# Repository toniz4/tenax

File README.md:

# Tenax

Tenax is a direct pin/diodeless split keyboard, based on the Blackpill dev board. with pinkie splay.

## Pictures

## Features

- No diodes
- Simple
  - No rgb
  - No oled
  - No buzzer (why someone would use this)
  - No having fun
- Cheap to build
- Moderate stagger
- Pinkie splay
- More memory, storage and clock than pro micro based boards
- Simple and comparatively fast to build

## Bill of Materials

| Component | Quantity | Comment |
|----------|-------------|------|
| Blackpill | 2 | [Weact Blackpills](https://pt.aliexpress.com/item/1005001456186625.html?spm=a2g0o.cart.0.0.4bff7f06OmOHkX&mp=1&gatewayAdapt=glo2bra) |
| (Optional) Round socket headers | 4 pieces with 20 slots | [Sockets](https://pt.aliexpress.com/item/32849903666.html?spm=a2g0o.productlist.0.0.5d201206BfLSLq&algo_pvid=ee920bf7-0efe-47ff-ae7a-32ff20382c14&algo_exp_id=ee920bf7-0efe-47ff-ae7a-32ff20382c14-2&pdp_ext_f=%7B%22sku_id%22%3A%2265196146337%22%7D&pdp_npi=2%40dis%21BRL%216.85%216.17%21%21%2122.31%21%21%402103143616643272838972410ea16a%2165196146337%21sea&curPageLogUid=SuAiwLt1kXaI) |
| PCB | 2 | [JLCPCB](https://jlcpcb.com/) |
| PJ-320A TRRS Jack | 2 | [TRRS Jack](https://pt.aliexpress.com/item/33029465106.html?spm=a2g0o.productlist.0.0.15fe3334PD2SG8&algo_pvid=7004b2d2-9c8b-4913-a9e2-3dc5fdaeaa0d&algo_exp_id=7004b2d2-9c8b-4913-a9e2-3dc5fdaeaa0d-1&pdp_ext_f=%7B%22sku_id%22%3A%2267273462020%22%7D&pdp_npi=2%40dis%21BRL%214.64%214.64%21%21%2126.84%21%21%402101e9d016643267206872835e58d8%2167273462020%21sea&curPageLogUid=0qIvsfpuA1ob) |
| Plates | 2 bottom plates 2 top plates | file ready to production in ./production/case/tenax-plates.dxf |
| 3mm M2 screws | 20 | [Screws](https://pt.aliexpress.com/item/32810852732.html?spm=a2g0o.productlist.0.0.628c2d0fWgxVas&algo_pvid=fbe3aa1a-175e-4711-af32-26884f1a49e6&algo_exp_id=fbe3aa1a-175e-4711-af32-26884f1a49e6-6&pdp_ext_f=%7B%22sku_id%22%3A%2212000027259563641%22%7D&pdp_npi=2%40dis%21BRL%2124.92%2119.42%21%21%2129.56%21%21%402101e9cf16643269855188818e5be6%2112000027259563641%21sea&curPageLogUid=PuCt3Ehw3DBV) |
| 8mm M2 standoffs | 10 | [Standoffs](https://pt.aliexpress.com/item/1005001478740318.html?spm=a2g0o.order_detail.0.0.41014c7f6cTJtM&gatewayAdapt=glo2bra) |
| Hotswap sockets | 36 | [Kailh Hotswap sockets](https://pt.aliexpress.com/item/4001051840976.html?spm=a2g0o.productlist.0.0.7e7d102dksVouM&algo_pvid=f8ac102a-3094-4209-a7b8-de68258d8b90&algo_exp_id=f8ac102a-3094-4209-a7b8-de68258d8b90-0&pdp_ext_f=%7B%22sku_id%22%3A%2210000013817160772%22%7D&pdp_npi=2%40dis%21BRL%2143.49%2143.49%21%21%21%21%21%40210318be16643268610471545ec83d%2110000013817160772%21sea&curPageLogUid=CIiwMxT5yDeo) |
| Switches | 36 | Any MX compatible switch will work |

## Build Guide

I'm too lazy to create a build guide, but the cantor keyboard build is similar, so it can
be used as reference, together with the hotswap sockets part on the corne guide.

- [Cantor guide](https://github.com/diepala/cantor/blob/main/doc/build_guide.md)
- [How to solder the hotswap sockets](https://github.com/foostan/crkbd/blob/main/corne-cherry/doc/v2/buildguide_en.md#kailh-pcb-socket)

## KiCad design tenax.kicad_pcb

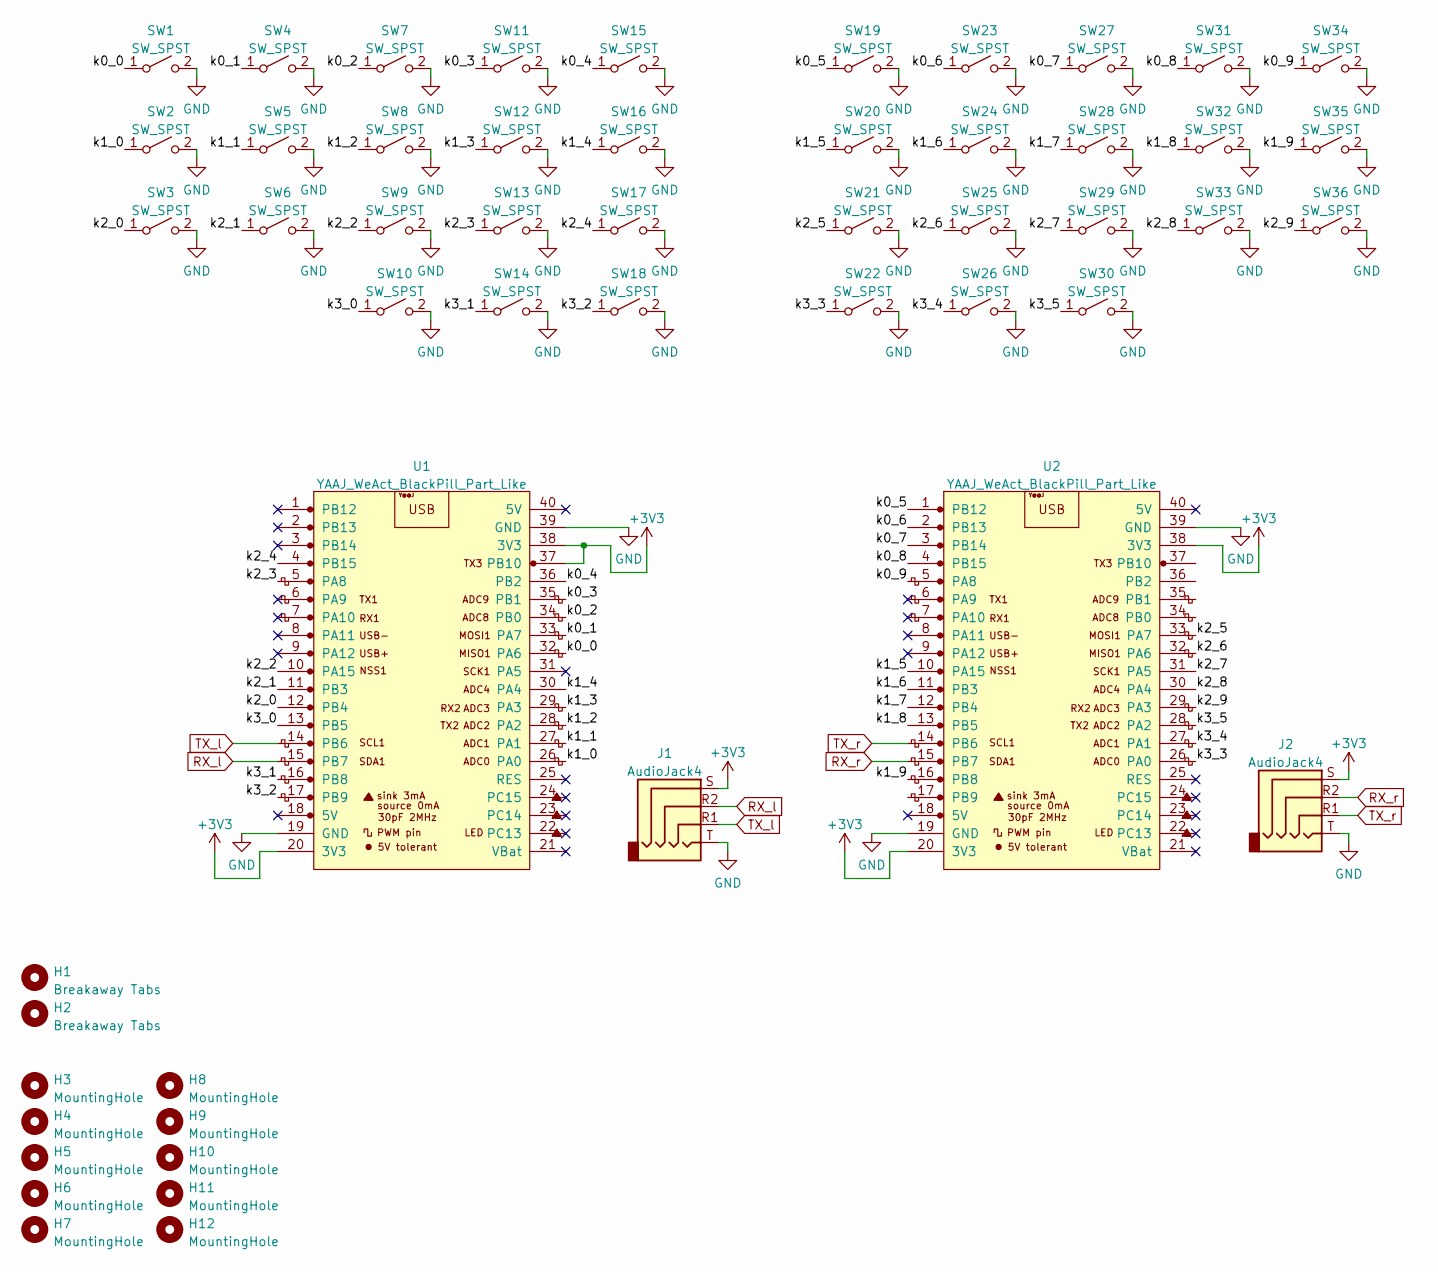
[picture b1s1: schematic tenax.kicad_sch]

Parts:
H1, H2: Breakaway Tabs; Breakaway_Tabs
H3, H4, H5, H6, H7, H8, H9, H10, H11, H12: MountingHole; M2_HOLE_v2
J1, J2: AudioJack4; MJ-4PP-9_1side
SW1, SW2, SW3, SW4, SW5, SW6, SW7, SW8, SW9, SW10, SW11, SW12, SW13, SW14, SW15, SW16, SW17, SW18, SW19, SW20, SW21, SW22, SW23, SW24, SW25, SW26, SW27, SW28, SW29, SW30, SW31, SW32, SW33, SW34, SW35, SW36: SW_SPST; CherryMX_Hotswap
U1, U2: YAAJ_WeAct_BlackPill_Part_Like; BlackPill_STLINK

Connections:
+3V3: J1.S, J2.S, U1.20 (3V3), U1.37 (PB10), U1.38 (3V3), U2.20 (3V3), U2.38 (3V3)
/k0_0: SW1.1 (A), U1.32 (PA6)
/k0_1: SW4.1 (A), U1.33 (PA7)
/k0_2: SW7.1 (A), U1.34 (PB0)
/k0_3: SW11.1 (A), U1.35 (PB1)
/k0_4: SW15.1 (A), U1.36 (PB2)
/k0_5: SW19.1 (A), U2.1 (PB12)
/k0_6: SW23.1 (A), U2.2 (PB13)
/k0_7: SW27.1 (A), U2.3 (PB14)
/k0_8: SW31.1 (A), U2.4 (PB15)
/k0_9: SW34.1 (A), U2.5 (PA8)
/k1_0: SW2.1 (A), U1.26 (PA0)
/k1_1: SW5.1 (A), U1.27 (PA1)
/k1_2: SW8.1 (A), U1.28 (PA2)
/k1_3: SW12.1 (A), U1.29 (PA3)
/k1_4: SW16.1 (A), U1.30 (PA4)
/k1_5: SW20.1 (A), U2.10 (PA15)
/k1_6: SW24.1 (A), U2.11 (PB3)
/k1_7: SW28.1 (A), U2.12 (PB4)
/k1_8: SW32.1 (A), U2.13 (PB5)
/k1_9: SW35.1 (A), U2.16 (PB8)
/k2_0: SW3.1 (A), U1.12 (PB4)
/k2_1: SW6.1 (A), U1.11 (PB3)
/k2_2: SW9.1 (A), U1.10 (PA15)
/k2_3: SW13.1 (A), U1.5 (PA8)
/k2_4: SW17.1 (A), U1.4 (PB15)
/k2_5: SW21.1 (A), U2.33 (PA7)
/k2_6: SW25.1 (A), U2.32 (PA6)
/k2_7: SW29.1 (A), U2.31 (PA5)
/k2_8: SW33.1 (A), U2.30 (PA4)
/k2_9: SW36.1 (A), U2.29 (PA3)
/k3_0: SW10.1 (A), U1.13 (PB5)
/k3_1: SW14.1 (A), U1.16 (PB8)
/k3_2: SW18.1 (A), U1.17 (PB9)
/k3_3: SW22.1 (A), U2.26 (PA0)
/k3_4: SW26.1 (A), U2.27 (PA1)
/k3_5: SW30.1 (A), U2.28 (PA2)
GND: J1.T, J2.T, SW1.2 (B), SW2.2 (B), SW3.2 (B), SW4.2 (B), SW5.2 (B), SW6.2 (B), SW7.2 (B), SW8.2 (B), SW9.2 (B), SW10.2 (B), SW11.2 (B), SW12.2 (B), SW13.2 (B), SW14.2 (B), SW15.2 (B), SW16.2 (B), SW17.2 (B), SW18.2 (B), SW19.2 (B), SW20.2 (B), SW21.2 (B), SW22.2 (B), SW23.2 (B), SW24.2 (B), SW25.2 (B), SW26.2 (B), SW27.2 (B), SW28.2 (B), SW29.2 (B), SW30.2 (B), SW31.2 (B), SW32.2 (B), SW33.2 (B), SW34.2 (B), SW35.2 (B), SW36.2 (B), U1.19 (GND), U1.39 (GND), U2.19 (GND), U2.39 (GND)
RX_l: J1.R2, U1.15 (PB7)
RX_r: J2.R2, U2.15 (PB7)
TX_l: J1.R1, U1.14 (PB6)
TX_r: J2.R1, U2.14 (PB6)

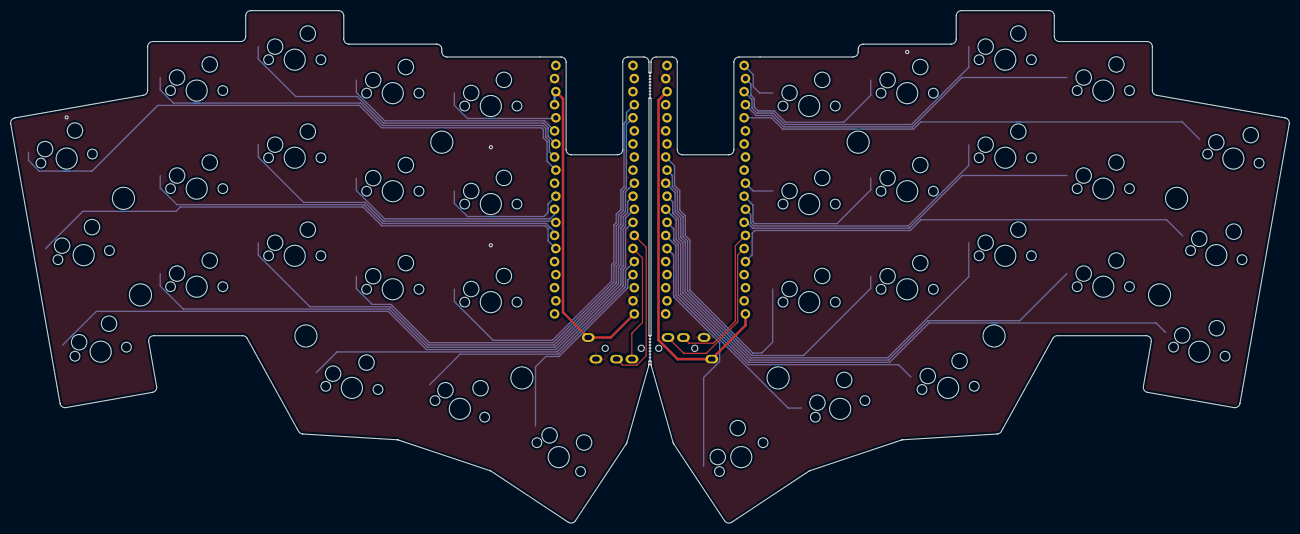
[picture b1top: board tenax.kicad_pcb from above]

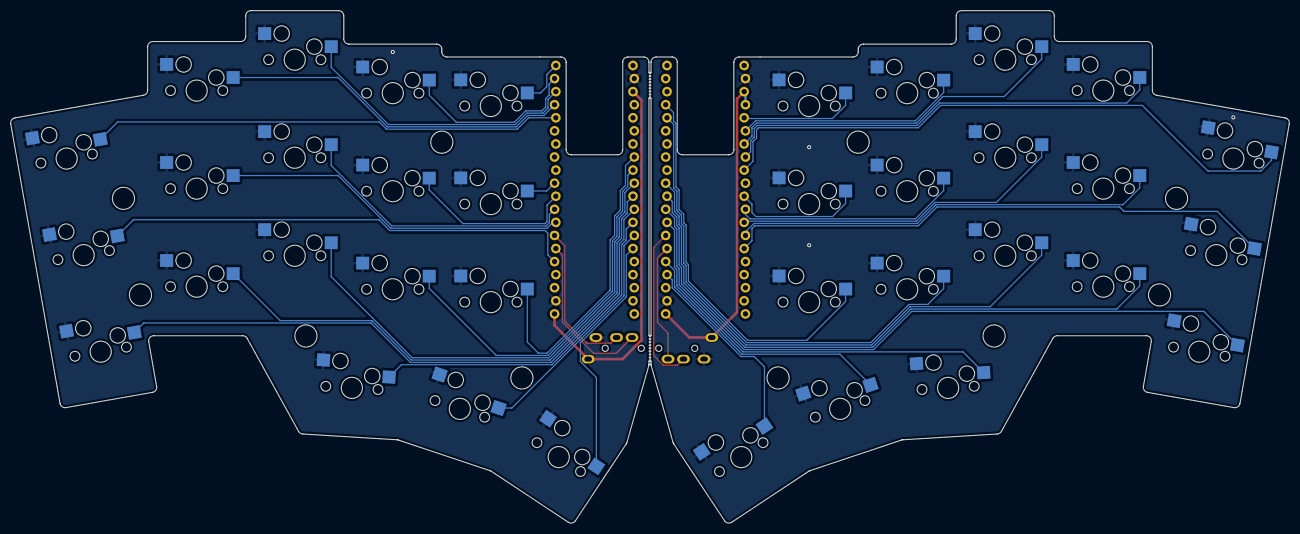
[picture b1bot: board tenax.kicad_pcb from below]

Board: 2 copper layers, 248.4 x 99.5 mm, 52 parts (2 on the bottom side), 42 nets.

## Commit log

2022-05-31 Last detais
2022-06-08 production version, fixed switch connected to B2
2022-09-24 fixed pcb
2022-09-28 add README.md
2022-09-28 fix quantity off standoffs
2022-11-29 fix spelling
